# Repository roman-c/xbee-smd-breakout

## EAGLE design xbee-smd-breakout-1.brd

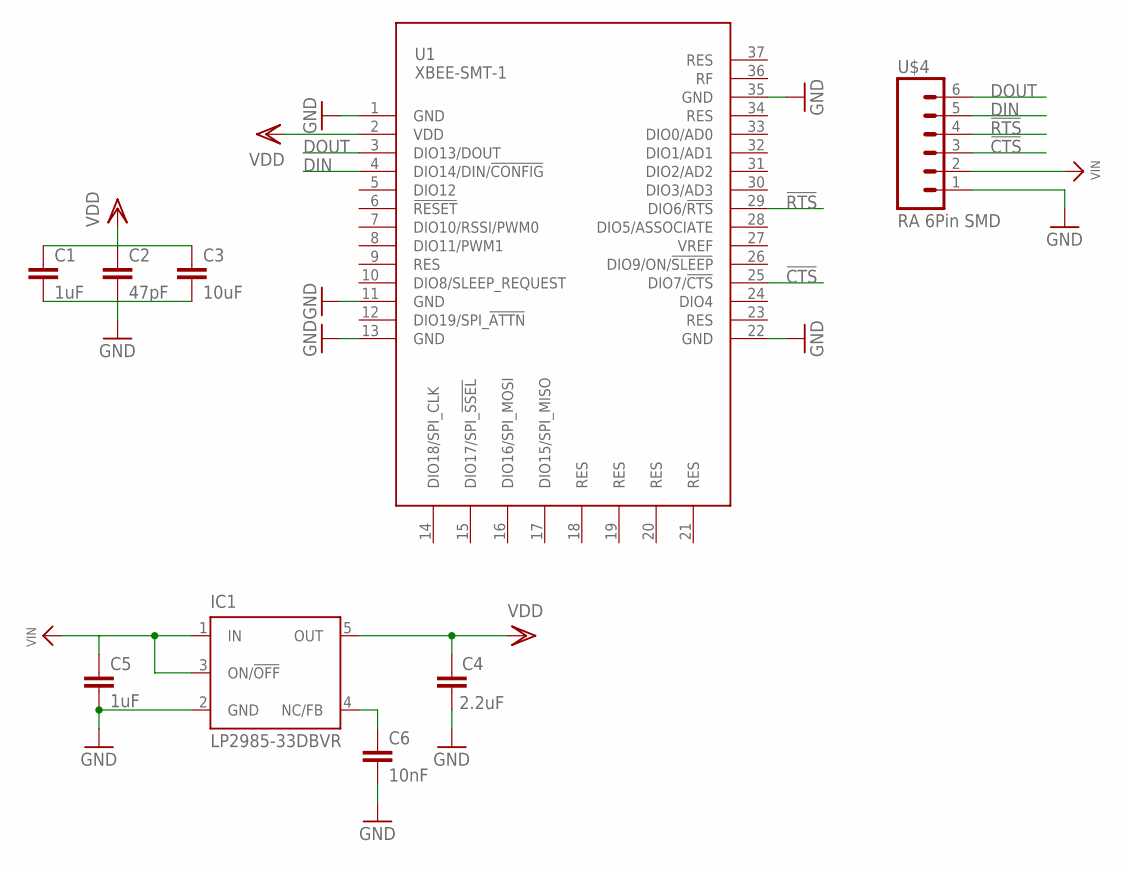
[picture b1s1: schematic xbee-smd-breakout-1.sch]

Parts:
C1, C5: 1uF; C0805
C2: 47pF; C0805
C3: 10uF; C0805
C4: 2.2uF; C0805; MPN MC0805B104K500CT
C6: 10nF; C0805
IC1: LP2985-33DBVR; SOT23-DBV; MPN ADP3309ARTZ-3.3-R7
U1: XBEE-SMT-1; XBEE-SMT
U$4: RA 6Pin SMD; 1X06-SMD

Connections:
!CTS: U1.25 (DIO7/!CTS), U$4.3
!RTS: U1.29 (DIO6/!RTS), U$4.4
DIN: U1.4 (DIO14/DIN/!CONFIG), U$4.5
DOUT: U1.3 (DIO13/DOUT), U$4.6
GND: C1.2, C2.2, C3.2, C4.1, C5.2, C6.2, IC1.2 (GND), U1.1 (GND), U1.11 (GND), U1.13 (GND), U1.22 (GND), U1.35 (GND), U$4.1
unnamed: C6.1, IC1.4 (NC/FB)
VDD: C1.1, C2.1, C3.1, C4.2, IC1.5 (OUT), U1.2 (VDD)
VIN: C5.1, IC1.1 (IN), IC1.3 (ON/!OFF), U$4.2

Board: 2 copper layers, 9 parts (0 on the bottom side), 8 nets, no tracks yet.

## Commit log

2015-11-01 v1 added

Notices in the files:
parts and their libraries:
SparkFun-Connectors: Licensing: Creative Commons ShareAlike 4.0 International - https://creativecommons.org/licenses/by-sa/4.0
microbuilder: This work is placed in the public domain, and may be freely used for commercial and non-commercial work with the following conditions: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
